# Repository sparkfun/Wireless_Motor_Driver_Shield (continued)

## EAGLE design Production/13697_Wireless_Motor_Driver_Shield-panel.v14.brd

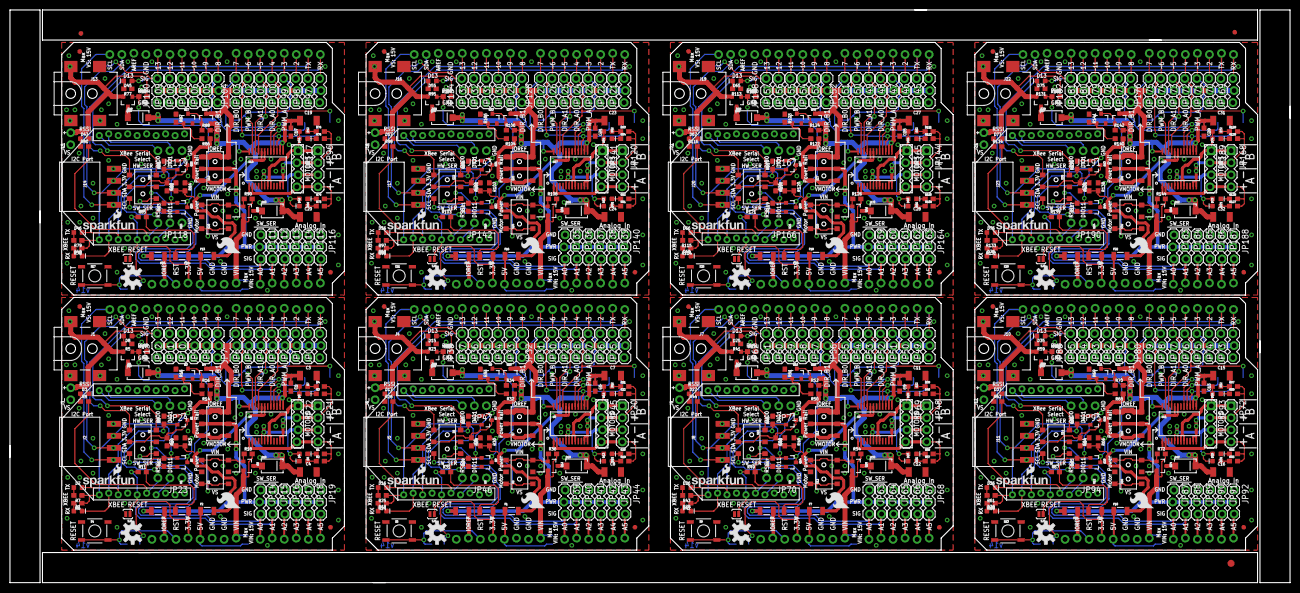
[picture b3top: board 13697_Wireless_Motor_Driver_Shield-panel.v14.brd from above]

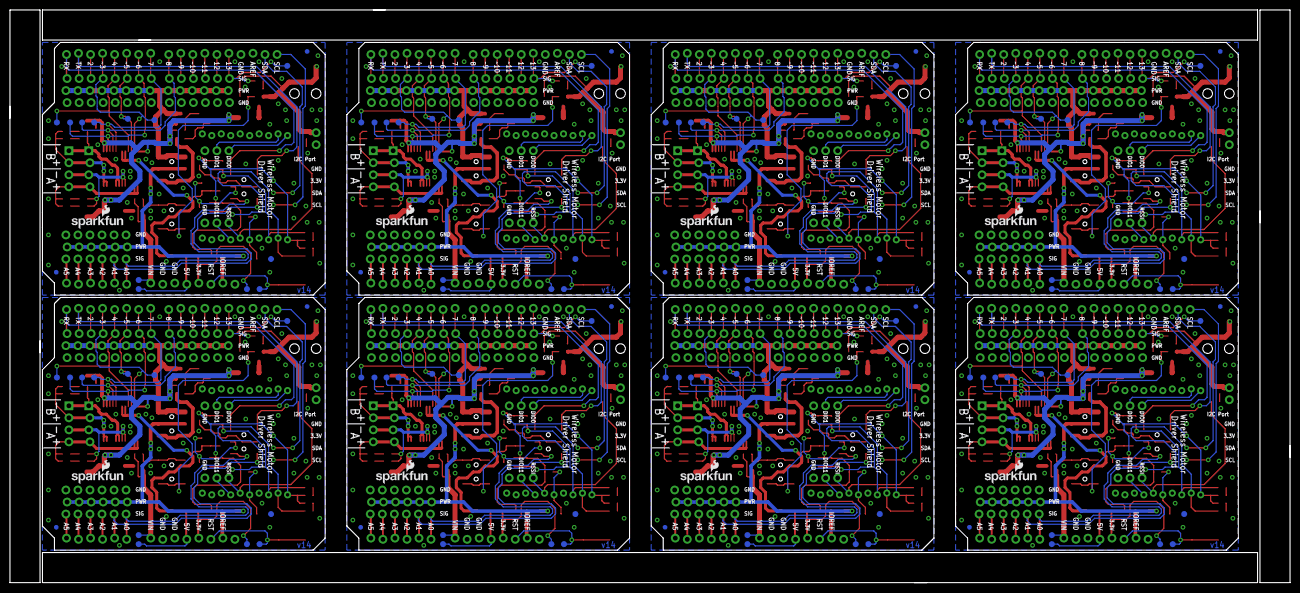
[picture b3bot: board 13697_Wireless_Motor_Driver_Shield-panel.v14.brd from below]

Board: 2 copper layers, 270.3 x 120.9 mm, 771 parts (120 on the bottom side), 496 nets.

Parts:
C1, C2, C5, C6, C9, C10, C13, C14, C17, C18, C21, C22, C25, C26, C29, C30: 0.1uF; 0603
C3, C4, C7, C8, C11, C12, C15, C16, C19, C20, C23, C24, C27, C28, C31, C32: 10uF; 1210
D1, D5, D7, D11, D12, D18, D21, D22, D28, D31, D32, D38, D41, D42, D48, D51, D52, D58, D61, D62, D68, D71, D72, D78: Yellow; LED-0603
D2, D8, D15, D16, D25, D26, D35, D36, D45, D46, D55, D56, D65, D66, D75, D76: GREEN; LED-0603
D3, D17, D27, D37, D47, D57, D67, D77: RED; LED-0603
D4, D6, D13, D14, D23, D24, D33, D34, D43, D44, D53, D54, D63, D64, D73, D74: BLUE; LED-0603
D9, D10, D19, D20, D29, D30, D39, D40, D49, D50, D59, D60, D69, D70, D79, D80: B340A; SMA-DIODE
E$1: FIDUCIAL-1.5X3
E$5, E$6: FIDUCIAL-1X2
F1, F2, F3, F4, F5, F6, F7, F8, F9, F10, F11, F12, F13, F14, F15, F16, F17, F18, F19, F20, F21, F22, F23, F24: PTC-1206
FID1, FID2, FID3, FID4, FID5, FID6, FID7, FID8, FID9, FID10, FID11, FID12, FID13, FID14, FID15, FID16, FID17, FID18, FID19, FID20, FID21, FID22, FID23, FID24, FID25, FID26, FID27, FID28, FID29, FID30, FID31, FID32: FIDUCIAL1X2; FIDUCIAL-1X2
J1, J4, J7, J10, J13, J16, J19, J22: 5.5x2.1mm Barrel; POWER_JACK_SMD
J2, J5, J8, J11, J14, J17, J20, J23: 1X04_SMD_RA_FEMALE
J3, J6, J9, J12, J15, J18, J21, J24: 1X02_NO_SILK
JP0, JP25, JP49, JP73, JP97, JP121, JP145, JP169: D0; 1X03_LOCK
JP1, JP26, JP50, JP74, JP98, JP122, JP146, JP170: D1; 1X03_LOCK
JP2, JP27, JP51, JP75, JP99, JP123, JP147, JP171: D2; 1X03_LOCK
JP3, JP28, JP52, JP76, JP100, JP124, JP148, JP172: D3; 1X03_LOCK
JP4, JP29, JP53, JP77, JP101, JP125, JP149, JP173: D4; 1X03_LOCK
JP5, JP30, JP54, JP78, JP102, JP126, JP150, JP174: D5; 1X03_LOCK
JP6, JP31, JP55, JP79, JP103, JP127, JP151, JP175: D6; 1X03_LOCK
JP7, JP32, JP56, JP80, JP104, JP128, JP152, JP176: D7; 1X03_LOCK
JP8, JP33, JP57, JP81, JP105, JP129, JP153, JP177: D8; 1X03_LOCK
JP9, JP34, JP58, JP82, JP106, JP130, JP154, JP178: D9; 1X03_LOCK
JP10, JP35, JP59, JP83, JP107, JP131, JP155, JP179: D10; 1X03_LOCK
JP11, JP36, JP60, JP84, JP108, JP132, JP156, JP180: D11; 1X03_LOCK
JP12, JP37, JP61, JP85, JP109, JP133, JP157, JP181: D12; 1X03_LOCK
JP13, JP38, JP62, JP86, JP110, JP134, JP158, JP182: D13; 1X03_LOCK
JP14, JP39, JP63, JP87, JP111, JP135, JP159, JP183: A0; 1X03_LOCK
JP15, JP40, JP64, JP88, JP112, JP136, JP160, JP184: A1; 1X03_LOCK
JP16, JP41, JP65, JP89, JP113, JP137, JP161, JP185: A2; 1X03_LOCK
JP17, JP42, JP66, JP90, JP114, JP138, JP162, JP186: A3; 1X03_LOCK
JP18, JP43, JP67, JP91, JP115, JP139, JP163, JP187: A4; 1X03_LOCK
JP19, JP44, JP68, JP92, JP116, JP140, JP164, JP188: A5; 1X03_LOCK
JP20, JP21, JP48, JP72, JP96, JP120, JP144, JP168: 1X04@1
JP22, JP45, JP69, JP93, JP117, JP141, JP165, JP189: 1X04_LOCK@1
JP23, JP24, JP46, JP47, JP70, JP71, JP94, JP95, JP118, JP119, JP142, JP143, JP166, JP167, JP190, JP191: 1X03_NO_SILK
LOGO1, LOGO5, LOGO9, LOGO13, LOGO17, LOGO21, LOGO25, LOGO29: OSHW-LOGOM; OSHW-LOGO-M
LOGO2, LOGO4, LOGO6, LOGO8, LOGO10, LOGO12, LOGO14, LOGO16, LOGO18, LOGO20, LOGO22, LOGO24, LOGO26, LOGO28, LOGO30, LOGO32: SFE_LOGO_NAME_FLAME.1_INCH; SFE_LOGO_NAME_FLAME_.1
LOGO3, LOGO7, LOGO11, LOGO15, LOGO19, LOGO23, LOGO27, LOGO31: SFE_LOGO_FLAME.2_INCH; SFE_LOGO_FLAME_.2
Q1, Q2, Q7, Q8, Q13, Q14, Q19, Q20, Q25, Q26, Q31, Q32, Q37, Q38, Q43, Q44: MOSFET-NCHANNELBSS138; SOT23-3
Q3, Q9, Q15, Q21, Q27, Q33, Q39, Q45: MMBT2222A; SOT23-3
Q4, Q5, Q6, Q10, Q11, Q12, Q16, Q17, Q18, Q22, Q23, Q24, Q28, Q29, Q30, Q34, Q35, Q36, Q40, Q41, Q42, Q46, Q47, Q48: DMG2307L; SOT23-3
R1, R2, R3, R4, R6, R7, R8, R9, R10, R11, R12, R13, R14, R19, R20, R21, R22, R24, R25, R26, R27, R28, R29, R30, R31, R32, R37, R38, R39, R40, R42, R43, R44, R45, R46, R47, R48, R49, R50, R55, R56, R57, R58, R60, R61, R62, R63, R64, R65, R66, R67, R68, R73, R74, R75, R76, R78, R79, R80, R81, R82, R83, R84, R85, R86, R91, R92, R93, R94, R96, R97, R98, R99, R100, R101, R102, R103, R104, R109, R110, R111, R112, R114, R115, R116, R117, R118, R119, R120, R121, R122, R127, R128, R129, R130, R132, R133, R134, R135, R136, R137, R138, R139, R140: 1k; 0603
R5, R23, R41, R59, R77, R95, R113, R131: 330; 0603
R15, R16, R17, R18, R33, R34, R35, R36, R51, R52, R53, R54, R69, R70, R71, R72, R87, R88, R89, R90, R105, R106, R107, R108, R123, R124, R125, R126, R141, R142, R143, R144: 10k; 0603
S1, S3, S7, S8, S11, S12, S15, S16, S19, S20, S23, S24, S27, S28, S31, S32: AYZ0202
S2, S6, S10, S14, S18, S22, S26, S30: DPDT; AYZ0202
S4, S5, S9, S13, S17, S21, S25, S29: RESET; TACTILE-SWITCH-SMD
SJ1, SJ2, SJ3, SJ4, SJ5, SJ6, SJ7, SJ8: SJ_2S-NO
TP1, TP2, TP3, TP4, TP5, TP6, TP7, TP8, TP9, TP10, TP11, TP12, TP13, TP14, TP15, TP16, TP17, TP18, TP19, TP20, TP21, TP22, TP23, TP24, TP25, TP26, TP27, TP28, TP29, TP30, TP31, TP32, TP33, TP34, TP35, TP36, TP37, TP38, TP39, TP40, TP41, TP42, TP43, TP44, TP45, TP46, TP47, TP48, TP49, TP50, TP51, TP52, TP53, TP54, TP55, TP56, TP57, TP58, TP59, TP60, TP61, TP62, TP63, TP64, TP65, TP66, TP67, TP68, TP69, TP70, TP71, TP72, TP73, TP74, TP75, TP76, TP77, TP78, TP79, TP80, TP81, TP82, TP83, TP84, TP85, TP86, TP87, TP88, TP89, TP90, TP91, TP92, TP93, TP94, TP95, TP96: PAD.03X.05
U1, U6, U9, U12, U15, U18, U21, U24: XBEE-1XBEE-1_LOCK; XBEE-1_LOCK
U2, U4, U7, U10, U13, U16, U19, U22: ARDUINO; UNO_R3_SHIELD_NOLABELS_LOCK
U3, U5, U8, U11, U14, U17, U20, U23: TB6612FNG; SSOP24

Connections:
3.3V: F3.1, TP11.P$1, U2.3.3V
3.3V1: F5.1, TP23.P$1, U4.3.3V
3.3V2: F8.1, TP35.P$1, U7.3.3V
3.3V3: F11.1, TP47.P$1, U10.3.3V
3.3V4: F14.1, TP59.P$1, U13.3.3V
3.3V5: F17.1, TP71.P$1, U16.3.3V
3.3V6: F20.1, TP83.P$1, U19.3.3V
3.3V7: F23.1, TP95.P$1, U22.3.3V
5V: F2.1, TP8.P$1, U2.5V
5V1: F1.1, TP20.P$1, U4.5V
5V2: F7.1, TP32.P$1, U7.5V
5V3: F10.1, TP44.P$1, U10.5V
5V4: F13.1, TP56.P$1, U13.5V
5V5: F16.1, TP68.P$1, U16.5V
5V6: F19.1, TP80.P$1, U19.5V
5V7: F22.1, TP92.P$1, U22.5V
A0/SW_RXI: JP14.3, S2.3, U2.A0
A0/SW_RXI1: JP39.3, S6.3, U4.A0
A0/SW_RXI2: JP63.3, S10.3, U7.A0
A0/SW_RXI3: JP87.3, S14.3, U10.A0
A0/SW_RXI4: JP111.3, S18.3, U13.A0
A0/SW_RXI5: JP135.3, S22.3, U16.A0
A0/SW_RXI6: JP159.3, S26.3, U19.A0
A0/SW_RXI7: JP183.3, S30.3, U22.A0
A1: JP44.3, U4.A5
A1/SW_TXO: JP15.3, S2.6, U2.A1
A1/SW_TXO1: JP40.3, S6.6, U4.A1
A1/SW_TXO2: JP64.3, S10.6, U7.A1
A1/SW_TXO3: JP88.3, S14.6, U10.A1
A1/SW_TXO4: JP112.3, S18.6, U13.A1
A1/SW_TXO5: JP136.3, S22.6, U16.A1
A1/SW_TXO6: JP160.3, S26.6, U19.A1
A1/SW_TXO7: JP184.3, S30.6, U22.A1
A2: JP16.3, U2.A2
A3: JP17.3, U2.A3
A4: JP18.3, U2.A4
A5: JP19.3, U2.A5
A6: JP43.3, U4.A4
A7: JP41.3, U4.A2
A8: JP42.3, U4.A3
A9: JP68.3, U7.A5
A10: JP67.3, U7.A4
A11: JP65.3, U7.A2
A12: JP66.3, U7.A3
A13: JP92.3, U10.A5
A14: JP91.3, U10.A4
A15: JP89.3, U10.A2
A16: JP90.3, U10.A3
A17: JP116.3, U13.A5
A18: JP115.3, U13.A4
A19: JP113.3, U13.A2
A20: JP114.3, U13.A3
A21: JP140.3, U16.A5
A22: JP139.3, U16.A4
A23: JP137.3, U16.A2
A24: JP138.3, U16.A3
A25: JP164.3, U19.A5
A26: JP163.3, U19.A4
A27: JP161.3, U19.A2
A28: JP162.3, U19.A3
A29: JP188.3, U22.A5
A30: JP187.3, U22.A4
A31: JP185.3, U22.A2
A32: JP186.3, U22.A3
AIN1: JP4.3, TP1.P$1, U2.D4, U3.21
AIN2: JP5.3, TP2.P$1, U2.D5, U3.22
AIN3: JP30.3, TP14.P$1, U4.D5, U5.22
AIN4: JP29.3, TP13.P$1, U4.D4, U5.21
AIN5: JP54.3, TP26.P$1, U7.D5, U8.22
AIN6: JP53.3, TP25.P$1, U7.D4, U8.21
AIN7: JP78.3, TP38.P$1, U10.D5, U11.22
AIN8: JP77.3, TP37.P$1, U10.D4, U11.21
AIN9: JP102.3, TP50.P$1, U13.D5, U14.22
AIN10: JP101.3, TP49.P$1, U13.D4, U14.21
AIN11: JP126.3, TP62.P$1, U16.D5, U17.22
AIN12: JP125.3, TP61.P$1, U16.D4, U17.21
AIN13: JP150.3, TP74.P$1, U19.D5, U20.22
AIN14: JP149.3, TP73.P$1, U19.D4, U20.21
AIN15: JP174.3, TP86.P$1, U22.D5, U23.22
AIN16: JP173.3, TP85.P$1, U22.D4, U23.21
AOUT1: JP21.4, JP22.4, R1.2, R2.2, U3.1, U3.2
AOUT2: D4.A, D5.C, JP21.3, JP22.3, U3.5, U3.6
AOUT3: JP20.4, JP45.4, R19.2, R20.2, U5.1, U5.2
AOUT4: D11.C, D13.A, JP20.3, JP45.3, U5.5, U5.6
AOUT5: JP48.4, JP69.4, R37.2, R38.2, U8.1, U8.2
AOUT6: D21.C, D23.A, JP48.3, JP69.3, U8.5, U8.6
AOUT7: JP72.4, JP93.4, R55.2, R56.2, U11.1, U11.2
AOUT8: D31.C, D33.A, JP72.3, JP93.3, U11.5, U11.6
AOUT9: JP96.4, JP117.4, R73.2, R74.2, U14.1, U14.2
AOUT10: D41.C, D43.A, JP96.3, JP117.3, U14.5, U14.6
AOUT11: JP120.4, JP141.4, R91.2, R92.2, U17.1, U17.2
AOUT12: D51.C, D53.A, JP120.3, JP141.3, U17.5, U17.6
AOUT13: JP144.4, JP165.4, R109.2, R110.2, U20.1, U20.2
AOUT14: D61.C, D63.A, JP144.3, JP165.3, U20.5, U20.6
AOUT15: JP168.4, JP189.4, R127.2, R128.2, U23.1, U23.2
AOUT16: D71.C, D73.A, JP168.3, JP189.3, U23.5, U23.6
BIN1: JP7.3, TP4.P$1, U2.D7, U3.17
BIN2: JP8.3, TP5.P$1, U2.D8, U3.16
BIN3: JP32.3, TP16.P$1, U4.D7, U5.17
BIN4: JP33.3, TP17.P$1, U4.D8, U5.16
BIN5: JP56.3, TP28.P$1, U7.D7, U8.17
BIN6: JP57.3, TP29.P$1, U7.D8, U8.16
BIN7: JP80.3, TP40.P$1, U10.D7, U11.17
BIN8: JP81.3, TP41.P$1, U10.D8, U11.16
BIN9: JP104.3, TP52.P$1, U13.D7, U14.17
BIN10: JP105.3, TP53.P$1, U13.D8, U14.16
BIN11: JP128.3, TP64.P$1, U16.D7, U17.17
BIN12: JP129.3, TP65.P$1, U16.D8, U17.16
BIN13: JP152.3, TP76.P$1, U19.D7, U20.17
BIN14: JP153.3, TP77.P$1, U19.D8, U20.16
BIN15: JP176.3, TP88.P$1, U22.D7, U23.17
BIN16: JP177.3, TP89.P$1, U22.D8, U23.16
BOUT1: JP21.2, JP22.2, R3.2, R4.2, U3.11, U3.12
BOUT2: D6.A, D7.C, JP21.1, JP22.1, U3.7, U3.8
BOUT3: D12.C, D14.A, JP20.1, JP45.1, U5.7, U5.8
BOUT4: JP20.2, JP45.2, R21.2, R22.2, U5.11, U5.12
BOUT5: D22.C, D24.A, JP48.1, JP69.1, U8.7, U8.8
BOUT6: JP48.2, JP69.2, R39.2, R40.2, U8.11, U8.12
BOUT7: D32.C, D34.A, JP72.1, JP93.1, U11.7, U11.8
BOUT8: JP72.2, JP93.2, R57.2, R58.2, U11.11, U11.12
BOUT9: D42.C, D44.A, JP96.1, JP117.1, U14.7, U14.8
BOUT10: JP96.2, JP117.2, R75.2, R76.2, U14.11, U14.12
BOUT11: D52.C, D54.A, JP120.1, JP141.1, U17.7, U17.8
BOUT12: JP120.2, JP141.2, R93.2, R94.2, U17.11, U17.12
BOUT13: D62.C, D64.A, JP144.1, JP165.1, U20.7, U20.8
BOUT14: JP144.2, JP165.2, R111.2, R112.2, U20.11, U20.12
BOUT15: D72.C, D74.A, JP168.1, JP189.1, U23.7, U23.8
BOUT16: JP168.2, JP189.2, R129.2, R130.2, U23.11, U23.12
D0/RXI: JP0.3, S2.1, U2.RX
D0/RXI1: JP25.3, S6.1, U4.RX
D0/RXI2: JP49.3, S10.1, U7.RX
D0/RXI3: JP73.3, S14.1, U10.RX
D0/RXI4: JP97.3, S18.1, U13.RX
D0/RXI5: JP121.3, S22.1, U16.RX
D0/RXI6: JP145.3, S26.1, U19.RX
D0/RXI7: JP169.3, S30.1, U22.RX
D1: JP37.3, U4.D12
D1/TXO: JP1.3, S2.4, U2.TX
D1/TXO1: JP26.3, S6.4, U4.TX
D1/TXO2: JP50.3, S10.4, U7.TX
D1/TXO3: JP74.3, S14.4, U10.TX
D1/TXO4: JP98.3, S18.4, U13.TX
D1/TXO5: JP122.3, S22.4, U16.TX
D1/TXO6: JP146.3, S26.4, U19.TX
D1/TXO7: JP170.3, S30.4, U22.TX
D2: JP2.3, U2.D2
D3: D15.A, JP38.3, TP19.P$1, U4.D13
D4: JP35.3, U4.D10
D5: JP27.3, U4.D2
D6: JP36.3, U4.D11
D7: JP34.3, U4.D9
D8: JP61.3, U7.D12
D9: JP9.3, U2.D9
D10: JP10.3, U2.D10
D11: JP11.3, U2.D11
D12: JP12.3, U2.D12
D13: D8.A, JP13.3, TP7.P$1, U2.D13
D14: D25.A, JP62.3, TP31.P$1, U7.D13
D15: JP59.3, U7.D10
D16: JP51.3, U7.D2
D17: JP60.3, U7.D11
D18: JP58.3, U7.D9
D19: JP85.3, U10.D12
D20: D35.A, JP86.3, TP43.P$1, U10.D13
D21: JP83.3, U10.D10
D22: JP75.3, U10.D2
D23: JP84.3, U10.D11
D24: JP82.3, U10.D9
D25: JP109.3, U13.D12
D26: D45.A, JP110.3, TP55.P$1, U13.D13
D27: JP107.3, U13.D10
D28: JP99.3, U13.D2
D29: JP108.3, U13.D11
D30: JP106.3, U13.D9
D31: JP133.3, U16.D12
D32: D55.A, JP134.3, TP67.P$1, U16.D13
D33: JP131.3, U16.D10
D34: JP123.3, U16.D2
D35: JP132.3, U16.D11
D36: JP130.3, U16.D9
D37: JP157.3, U19.D12
D38: D65.A, JP158.3, TP79.P$1, U19.D13
D39: JP155.3, U19.D10
D40: JP147.3, U19.D2
D41: JP156.3, U19.D11
D42: JP154.3, U19.D9
D43: JP181.3, U22.D12
D44: D75.A, JP182.3, TP91.P$1, U22.D13
D45: JP179.3, U22.D10
D46: JP171.3, U22.D2
D47: JP180.3, U22.D11
D48: JP178.3, U22.D9
DIN: D2.C, Q1.2, R9.1, U1.3
DIN1: D16.C, Q7.2, R27.1, U6.3
DIN2: D26.C, Q13.2, R45.1, U9.3
DIN3: D36.C, Q19.2, R63.1, U12.3
DIN4: D46.C, Q25.2, R81.1, U15.3
DIN5: D56.C, Q31.2, R99.1, U18.3
DIN6: D66.C, Q37.2, R117.1, U21.3
DIN7: D76.C, Q43.2, R135.1, U24.3
DIO0: JP24.3, U1.20
DIO1: JP24.2, U1.19
DIO2: JP46.2, U6.7
DIO3: JP47.3, U6.20
DIO4: JP47.2, U6.19
DIO5: JP70.2, U9.7
DIO6: JP71.3, U9.20
DIO7: JP71.2, U9.19
DIO8: JP94.2, U12.7
DIO9: JP95.3, U12.20
DIO10: JP95.2, U12.19
DIO11: JP23.2, U1.7
DIO12: JP118.2, U15.7
DIO13: JP119.3, U15.20
DIO14: JP119.2, U15.19
DIO15: JP142.2, U18.7
DIO16: JP143.3, U18.20
DIO17: JP143.2, U18.19
DIO18: JP166.2, U21.7
DIO19: JP167.3, U21.20
DIO20: JP167.2, U21.19
DIO21: JP190.2, U24.7
DIO22: JP191.3, U24.20
DIO23: JP191.2, U24.19
DOUT: D1.C, Q2.2, R12.1, U1.2
DOUT1: D18.C, Q8.2, R29.1, U6.2
DOUT2: D28.C, Q14.2, R47.1, U9.2
DOUT3: D38.C, Q20.2, R65.1, U12.2
DOUT4: D48.C, Q26.2, R83.1, U15.2
DOUT5: D58.C, Q32.2, R101.1, U18.2
DOUT6: D68.C, Q38.2, R119.1, U21.2
DOUT7: D78.C, Q44.2, R137.1, U24.2
FUSED_3.3V: F3.2, J2.2, Q1.1, Q2.1, R6.1, R7.1, R9.2, R11.2, R12.2, U1.1
FUSED_3.3V1: F5.2, J5.2, Q7.1, Q8.1, R24.1, R25.1, R27.2, R29.2, R31.2, U6.1
FUSED_3.3V2: F8.2, J8.2, Q13.1, Q14.1, R42.1, R43.1, R45.2, R47.2, R49.2, U9.1
FUSED_3.3V3: F11.2, J11.2, Q19.1, Q20.1, R60.1, R61.1, R63.2, R65.2, R67.2, U12.1
FUSED_3.3V4: F14.2, J14.2, Q25.1, Q26.1, R78.1, R79.1, R81.2, R83.2, R85.2, U15.1
FUSED_3.3V5: F17.2, J17.2, Q31.1, Q32.1, R96.1, R97.1, R99.2, R101.2, R103.2, U18.1
FUSED_3.3V6: F20.2, J20.2, Q37.1, Q38.1, R114.1, R115.1, R117.2, R119.2, R121.2, U21.1
FUSED_3.3V7: F23.2, J23.2, Q43.1, Q44.1, R132.1, R133.1, R135.2, R137.2, R139.2, U24.1
FUSED_5V: C2.1, F2.2, R10.2, R13.2, U3.19, U3.20
FUSED_5V1: C6.1, F1.2, R28.2, R30.2, U5.19, U5.20
FUSED_5V2: C10.1, F7.2, R46.2, R48.2, U8.19, U8.20
FUSED_5V3: C14.1, F10.2, R64.2, R66.2, U11.19, U11.20
FUSED_5V4: C18.1, F13.2, R82.2, R84.2, U14.19, U14.20
FUSED_5V5: C22.1, F16.2, R100.2, R102.2, U17.19, U17.20
FUSED_5V6: C26.1, F19.2, R118.2, R120.2, U20.19, U20.20
FUSED_5V7: C30.1, F22.2, R136.2, R138.2, U23.19, U23.20
FUSED_IOREF: F4.2, JP14.2, JP15.2, JP16.2, JP17.2, JP18.2, JP19.2, S1.2, S1.5
FUSED_IOREF1: F6.2, JP39.2, JP40.2, JP41.2, JP42.2, JP43.2, JP44.2, S7.2, S7.5
FUSED_IOREF2: F9.2, JP63.2, JP64.2, JP65.2, JP66.2, JP67.2, JP68.2, S11.2, S11.5
FUSED_IOREF3: F12.2, JP87.2, JP88.2, JP89.2, JP90.2, JP91.2, JP92.2, S15.2, S15.5
FUSED_IOREF4: F15.2, JP111.2, JP112.2, JP113.2, JP114.2, JP115.2, JP116.2, S19.2, S19.5
FUSED_IOREF5: F18.2, JP135.2, JP136.2, JP137.2, JP138.2, JP139.2, JP140.2, S23.2, S23.5
FUSED_IOREF6: F21.2, JP159.2, JP160.2, JP161.2, JP162.2, JP163.2, JP164.2, S27.2, S27.5
FUSED_IOREF7: F24.2, JP183.2, JP184.2, JP185.2, JP186.2, JP187.2, JP188.2, S31.2, S31.5
GND: C1.2, C2.2, C3.2, C4.2, D3.C, J1.GND, J2.1, J3.1, JP0.1, JP1.1, JP2.1, JP3.1, JP4.1, JP5.1, JP6.1, JP7.1, JP8.1, JP9.1, JP10.1, JP11.1, JP12.1, JP13.1, JP14.1, JP15.1, JP16.1, JP17.1, JP18.1, JP19.1, JP23.1, JP24.1, Q3.2, R5.1, R15.1, S3.2, S3.5, S4.1, S4.2, SJ5.2, TP9.P$1, U1.10, U2.GND@0, U2.GND@1, U2.GND@2, U3.3, U3.4, U3.9, U3.10, U3.18
GND1: C5.2, C6.2, C7.2, C8.2, D17.C, J4.GND, J5.1, J6.1, JP25.1, JP26.1, JP27.1, JP28.1, JP29.1, JP30.1, JP31.1, JP32.1, JP33.1, JP34.1, JP35.1, JP36.1, JP37.1, JP38.1, JP39.1, JP40.1, JP41.1, JP42.1, JP43.1, JP44.1, JP46.1, JP47.1, Q9.2, R23.1, R33.1, S5.1, S5.2, S8.2, S8.5, SJ1.2, TP21.P$1, U4.GND@0, U4.GND@1, U4.GND@2, U5.3, U5.4, U5.9, U5.10, U5.18, U6.10
GND2: C9.2, C10.2, C11.2, C12.2, D27.C, J7.GND, J8.1, J9.1, JP49.1, JP50.1, JP51.1, JP52.1, JP53.1, JP54.1, JP55.1, JP56.1, JP57.1, JP58.1, JP59.1, JP60.1, JP61.1, JP62.1, JP63.1, JP64.1, JP65.1, JP66.1, JP67.1, JP68.1, JP70.1, JP71.1, Q15.2, R41.1, R51.1, S9.1, S9.2, S12.2, S12.5, SJ2.2, TP33.P$1, U7.GND@0, U7.GND@1, U7.GND@2, U8.3, U8.4, U8.9, U8.10, U8.18, U9.10
GND3: C13.2, C14.2, C15.2, C16.2, D37.C, J10.GND, J11.1, J12.1, JP73.1, JP74.1, JP75.1, JP76.1, JP77.1, JP78.1, JP79.1, JP80.1, JP81.1, JP82.1, JP83.1, JP84.1, JP85.1, JP86.1, JP87.1, JP88.1, JP89.1, JP90.1, JP91.1, JP92.1, JP94.1, JP95.1, Q21.2, R59.1, R69.1, S13.1, S13.2, S16.2, S16.5, SJ3.2, TP45.P$1, U10.GND@0, U10.GND@1, U10.GND@2, U11.3, U11.4, U11.9, U11.10, U11.18, U12.10
GND4: C17.2, C18.2, C19.2, C20.2, D47.C, J13.GND, J14.1, J15.1, JP97.1, JP98.1, JP99.1, JP100.1, JP101.1, JP102.1, JP103.1, JP104.1, JP105.1, JP106.1, JP107.1, JP108.1, JP109.1, JP110.1, JP111.1, JP112.1, JP113.1, JP114.1, JP115.1, JP116.1, JP118.1, JP119.1, Q27.2, R77.1, R87.1, S17.1, S17.2, S20.2, S20.5, SJ4.2, TP57.P$1, U13.GND@0, U13.GND@1, U13.GND@2, U14.3, U14.4, U14.9, U14.10, U14.18, U15.10
GND5: C21.2, C22.2, C23.2, C24.2, D57.C, J16.GND, J17.1, J18.1, JP121.1, JP122.1, JP123.1, JP124.1, JP125.1, JP126.1, JP127.1, JP128.1, JP129.1, JP130.1, JP131.1, JP132.1, JP133.1, JP134.1, JP135.1, JP136.1, JP137.1, JP138.1, JP139.1, JP140.1, JP142.1, JP143.1, Q33.2, R95.1, R105.1, S21.1, S21.2, S24.2, S24.5, SJ6.2, TP69.P$1, U16.GND@0, U16.GND@1, U16.GND@2, U17.3, U17.4, U17.9, U17.10, U17.18, U18.10
GND6: C25.2, C26.2, C27.2, C28.2, D67.C, J19.GND, J20.1, J21.1, JP145.1, JP146.1, JP147.1, JP148.1, JP149.1, JP150.1, JP151.1, JP152.1, JP153.1, JP154.1, JP155.1, JP156.1, JP157.1, JP158.1, JP159.1, JP160.1, JP161.1, JP162.1, JP163.1, JP164.1, JP166.1, JP167.1, Q39.2, R113.1, R123.1, S25.1, S25.2, S28.2, S28.5, SJ7.2, TP81.P$1, U19.GND@0, U19.GND@1, U19.GND@2, U20.3, U20.4, U20.9, U20.10, U20.18, U21.10
GND7: C29.2, C30.2, C31.2, C32.2, D77.C, J22.GND, J23.1, J24.1, JP169.1, JP170.1, JP171.1, JP172.1, JP173.1, JP174.1, JP175.1, JP176.1, JP177.1, JP178.1, JP179.1, JP180.1, JP181.1, JP182.1, JP183.1, JP184.1, JP185.1, JP186.1, JP187.1, JP188.1, JP190.1, JP191.1, Q45.2, R131.1, R141.1, S29.1, S29.2, S32.2, S32.5, SJ8.2, TP93.P$1, U22.GND@0, U22.GND@1, U22.GND@2, U23.3, U23.4, U23.9, U23.10, U23.18, U24.10
IOREF: F4.1, U2.IOREF
IOREF1: F6.1, U4.IOREF
IOREF2: F9.1, U7.IOREF
IOREF3: F12.1, U10.IOREF
IOREF4: F15.1, U13.IOREF
IOREF5: F18.1, U16.IOREF
IOREF6: F21.1, U19.IOREF
IOREF7: F24.1, U22.IOREF
unnamed: D8.C, R5.2
unnamed: Q3.1, R14.2, R15.2
unnamed: D5.A, R2.1
unnamed: Q6.1, R18.1, S3.3, S3.6
unnamed: D4.C, R1.1
unnamed: D7.A, R4.1
unnamed: D6.C, R3.1
unnamed: J1.VIN0, J3.2, Q5.2, R17.2
unnamed: Q3.3, Q4.1, R16.1
unnamed: Q5.1, R17.1, S3.1, S3.4
unnamed: R14.1, S1.1, S1.4
unnamed: D9.A, Q5.3
unnamed: D10.A, Q6.3
unnamed: D11.A, R19.1
unnamed: D13.C, R20.1
unnamed: D12.A, R21.1
unnamed: D14.C, R22.1
unnamed: D15.C, R23.2
unnamed: D1.A, R6.2
unnamed: D18.A, R24.2
unnamed: D16.A, R25.2
unnamed: D17.A, R26.1
unnamed: Q9.1, R32.2, R33.2
unnamed: Q9.3, Q10.1, R34.1
unnamed: R32.1, S7.1, S7.4
unnamed: J4.VIN0, J6.2, Q11.2, R35.2
unnamed: Q11.1, R35.1, S8.1, S8.4
unnamed: Q12.1, R36.1, S8.3, S8.6
unnamed: D19.A, Q11.3
unnamed: D20.A, Q12.3
unnamed: D21.A, R37.1
unnamed: D23.C, R38.1
unnamed: D22.A, R39.1
unnamed: D24.C, R40.1
unnamed: D25.C, R41.2
unnamed: D28.A, R42.2
unnamed: D26.A, R43.2
unnamed: D27.A, R44.1
unnamed: D2.A, R7.2
unnamed: D3.A, R8.1
unnamed: Q15.1, R50.2, R51.2
unnamed: Q15.3, Q16.1, R52.1
unnamed: R50.1, S11.1, S11.4
unnamed: J7.VIN0, J9.2, Q17.2, R53.2
unnamed: Q17.1, R53.1, S12.1, S12.4
unnamed: Q18.1, R54.1, S12.3, S12.6
unnamed: D29.A, Q17.3
unnamed: D30.A, Q18.3
unnamed: D31.A, R55.1
unnamed: D33.C, R56.1
unnamed: D32.A, R57.1
unnamed: D34.C, R58.1
unnamed: D35.C, R59.2
unnamed: D38.A, R60.2
unnamed: D36.A, R61.2
unnamed: D37.A, R62.1
unnamed: Q21.1, R68.2, R69.2
unnamed: Q21.3, Q22.1, R70.1
unnamed: R68.1, S15.1, S15.4
unnamed: J10.VIN0, J12.2, Q23.2, R71.2
unnamed: Q23.1, R71.1, S16.1, S16.4
unnamed: Q24.1, R72.1, S16.3, S16.6
unnamed: D39.A, Q23.3
unnamed: D40.A, Q24.3
unnamed: D41.A, R73.1
unnamed: D43.C, R74.1
unnamed: D42.A, R75.1
unnamed: D44.C, R76.1
unnamed: D45.C, R77.2
unnamed: D48.A, R78.2
unnamed: D46.A, R79.2
unnamed: D47.A, R80.1
unnamed: Q27.1, R86.2, R87.2
unnamed: Q27.3, Q28.1, R88.1
unnamed: R86.1, S19.1, S19.4
unnamed: J13.VIN0, J15.2, Q29.2, R89.2
unnamed: Q29.1, R89.1, S20.1, S20.4
unnamed: Q30.1, R90.1, S20.3, S20.6
unnamed: D49.A, Q29.3
unnamed: D50.A, Q30.3
unnamed: D51.A, R91.1
unnamed: D53.C, R92.1
unnamed: D52.A, R93.1
unnamed: D54.C, R94.1
unnamed: D55.C, R95.2
unnamed: D58.A, R96.2
unnamed: D56.A, R97.2
unnamed: D57.A, R98.1
unnamed: Q33.1, R104.2, R105.2
unnamed: Q33.3, Q34.1, R106.1
unnamed: R104.1, S23.1, S23.4
unnamed: J16.VIN0, J18.2, Q35.2, R107.2
unnamed: Q35.1, R107.1, S24.1, S24.4
unnamed: Q36.1, R108.1, S24.3, S24.6
unnamed: D59.A, Q35.3
unnamed: D60.A, Q36.3
unnamed: D61.A, R109.1
unnamed: D63.C, R110.1
unnamed: D62.A, R111.1
unnamed: D64.C, R112.1
unnamed: D65.C, R113.2
unnamed: D68.A, R114.2
unnamed: D66.A, R115.2
unnamed: D67.A, R116.1
unnamed: Q39.1, R122.2, R123.2
unnamed: Q39.3, Q40.1, R124.1
unnamed: R122.1, S27.1, S27.4
unnamed: J19.VIN0, J21.2, Q41.2, R125.2
unnamed: Q41.1, R125.1, S28.1, S28.4
unnamed: Q42.1, R126.1, S28.3, S28.6
unnamed: D69.A, Q41.3
unnamed: D70.A, Q42.3
unnamed: D71.A, R127.1
unnamed: D73.C, R128.1
unnamed: D72.A, R129.1
unnamed: D74.C, R130.1
unnamed: D75.C, R131.2
unnamed: D78.A, R132.2
unnamed: D76.A, R133.2
unnamed: D77.A, R134.1
unnamed: Q45.1, R140.2, R141.2
unnamed: Q45.3, Q46.1, R142.1
unnamed: R140.1, S31.1, S31.4
unnamed: J22.VIN0, J24.2, Q47.2, R143.2
unnamed: Q47.1, R143.1, S32.1, S32.4
unnamed: Q48.1, R144.1, S32.3, S32.6
unnamed: D79.A, Q47.3
unnamed: D80.A, Q48.3
PWMA: JP3.3, TP3.P$1, U2.D3, U3.23
PWMA1: JP28.3, TP15.P$1, U4.D3, U5.23
PWMA2: JP52.3, TP27.P$1, U7.D3, U8.23
PWMA3: JP76.3, TP39.P$1, U10.D3, U11.23
PWMA4: JP100.3, TP51.P$1, U13.D3, U14.23
PWMA5: JP124.3, TP63.P$1, U16.D3, U17.23
PWMA6: JP148.3, TP75.P$1, U19.D3, U20.23
PWMA7: JP172.3, TP87.P$1, U22.D3, U23.23
PWMB: JP6.3, TP6.P$1, U2.D6, U3.15
PWMB1: JP31.3, TP18.P$1, U4.D6, U5.15
PWMB2: JP55.3, TP30.P$1, U7.D6, U8.15
PWMB3: JP79.3, TP42.P$1, U10.D6, U11.15
PWMB4: JP103.3, TP54.P$1, U13.D6, U14.15
PWMB5: JP127.3, TP66.P$1, U16.D6, U17.15
PWMB6: JP151.3, TP78.P$1, U19.D6, U20.15
PWMB7: JP175.3, TP90.P$1, U22.D6, U23.15
PWR_RAIL: JP0.2, JP1.2, JP2.2, JP3.2, JP4.2, JP5.2, JP6.2, JP7.2, JP8.2, JP9.2, JP10.2, JP11.2, JP12.2, JP13.2, Q4.3, S1.3, S1.6
PWR_RAIL1: JP25.2, JP26.2, JP27.2, JP28.2, JP29.2, JP30.2, JP31.2, JP32.2, JP33.2, JP34.2, JP35.2, JP36.2, JP37.2, JP38.2, Q10.3, S7.3, S7.6
PWR_RAIL2: JP49.2, JP50.2, JP51.2, JP52.2, JP53.2, JP54.2, JP55.2, JP56.2, JP57.2, JP58.2, JP59.2, JP60.2, JP61.2, JP62.2, Q16.3, S11.3, S11.6
PWR_RAIL3: JP73.2, JP74.2, JP75.2, JP76.2, JP77.2, JP78.2, JP79.2, JP80.2, JP81.2, JP82.2, JP83.2, JP84.2, JP85.2, JP86.2, Q22.3, S15.3, S15.6
PWR_RAIL4: JP97.2, JP98.2, JP99.2, JP100.2, JP101.2, JP102.2, JP103.2, JP104.2, JP105.2, JP106.2, JP107.2, JP108.2, JP109.2, JP110.2, Q28.3, S19.3, S19.6
PWR_RAIL5: JP121.2, JP122.2, JP123.2, JP124.2, JP125.2, JP126.2, JP127.2, JP128.2, JP129.2, JP130.2, JP131.2, JP132.2, JP133.2, JP134.2, Q34.3, S23.3, S23.6
PWR_RAIL6: JP145.2, JP146.2, JP147.2, JP148.2, JP149.2, JP150.2, JP151.2, JP152.2, JP153.2, JP154.2, JP155.2, JP156.2, JP157.2, JP158.2, Q40.3, S27.3, S27.6
PWR_RAIL7: JP169.2, JP170.2, JP171.2, JP172.2, JP173.2, JP174.2, JP175.2, JP176.2, JP177.2, JP178.2, JP179.2, JP180.2, JP181.2, JP182.2, Q46.3, S31.3, S31.6
RESET: S4.3, S4.4, TP12.P$1, U2.RES
RESET1: S5.3, S5.4, TP24.P$1, U4.RES
RESET2: S9.3, S9.4, TP36.P$1, U7.RES
RESET3: S13.3, S13.4, TP48.P$1, U10.RES
RESET4: S17.3, S17.4, TP60.P$1, U13.RES
RESET5: S21.3, S21.4, TP72.P$1, U16.RES
RESET6: S25.3, S25.4, TP84.P$1, U19.RES
RESET7: S29.3, S29.4, TP96.P$1, U22.RES
RSSI: JP23.3, R8.2, U1.6
RSSI1: JP46.3, R26.2, U6.6
RSSI2: JP70.3, R44.2, U9.6
RSSI3: JP94.3, R62.2, U12.6
RSSI4: JP118.3, R80.2, U15.6
RSSI5: JP142.3, R98.2, U18.6
RSSI6: JP166.3, R116.2, U21.6
RSSI7: JP190.3, R134.2, U24.6
SCL: J2.4, U2.SCL
SCL1: J5.4, U4.SCL
SCL2: J8.4, U7.SCL
SCL3: J11.4, U10.SCL
SCL4: J14.4, U13.SCL
SCL5: J17.4, U16.SCL
SCL6: J20.4, U19.SCL
SCL7: J23.4, U22.SCL
SDA: J2.3, U2.SDA
SDA1: J5.3, U4.SDA
SDA2: J8.3, U7.SDA
SDA3: J11.3, U10.SDA
SDA4: J14.3, U13.SDA
SDA5: J17.3, U16.SDA
SDA6: J20.3, U19.SDA
SDA7: J23.3, U22.SDA
VIN: Q6.2, R18.2, TP10.P$1, U2.VIN
VIN1: Q12.2, R36.2, TP22.P$1, U4.VIN
VIN2: Q18.2, R54.2, TP34.P$1, U7.VIN
VIN3: Q24.2, R72.2, TP46.P$1, U10.VIN
VIN4: Q30.2, R90.2, TP58.P$1, U13.VIN
VIN5: Q36.2, R108.2, TP70.P$1, U16.VIN
VIN6: Q42.2, R126.2, TP82.P$1, U19.VIN
VIN7: Q48.2, R144.2, TP94.P$1, U22.VIN
VMOTOR: C1.1, C3.1, C4.1, D9.C, D10.C, Q4.2, R16.2, U3.13, U3.14, U3.24
VMOTOR1: C5.1, C7.1, C8.1, D19.C, D20.C, Q10.2, R34.2, U5.13, U5.14, U5.24
VMOTOR2: C9.1, C11.1, C12.1, D29.C, D30.C, Q16.2, R52.2, U8.13, U8.14, U8.24
VMOTOR3: C13.1, C15.1, C16.1, D39.C, D40.C, Q22.2, R70.2, U11.13, U11.14, U11.24
VMOTOR4: C17.1, C19.1, C20.1, D49.C, D50.C, Q28.2, R88.2, U14.13, U14.14, U14.24
VMOTOR5: C21.1, C23.1, C24.1, D59.C, D60.C, Q34.2, R106.2, U17.13, U17.14, U17.24
VMOTOR6: C25.1, C27.1, C28.1, D69.C, D70.C, Q40.2, R124.2, U20.13, U20.14, U20.24
VMOTOR7: C29.1, C31.1, C32.1, D79.C, D80.C, Q46.2, R142.2, U23.13, U23.14, U23.24
XBEE_RESET: R11.1, SJ5.1, U1.5
XBEE_RESET1: R31.1, SJ1.1, U6.5
XBEE_RESET2: R49.1, SJ2.1, U9.5
XBEE_RESET3: R67.1, SJ3.1, U12.5
XBEE_RESET4: R85.1, SJ4.1, U15.5
XBEE_RESET5: R103.1, SJ6.1, U18.5
XBEE_RESET6: R121.1, SJ7.1, U21.5
XBEE_RESET7: R139.1, SJ8.1, U24.5
XBEE_RXI: Q2.3, R13.1, S2.2
XBEE_RXI1: Q8.3, R30.1, S6.2
XBEE_RXI2: Q14.3, R48.1, S10.2
XBEE_RXI3: Q20.3, R66.1, S14.2
XBEE_RXI4: Q26.3, R84.1, S18.2
XBEE_RXI5: Q32.3, R102.1, S22.2
XBEE_RXI6: Q38.3, R120.1, S26.2
XBEE_RXI7: Q44.3, R138.1, S30.2
XBEE_TXO: Q1.3, R10.1, S2.5
XBEE_TXO1: Q7.3, R28.1, S6.5
XBEE_TXO2: Q13.3, R46.1, S10.5
XBEE_TXO3: Q19.3, R64.1, S14.5
XBEE_TXO4: Q25.3, R82.1, S18.5
XBEE_TXO5: Q31.3, R100.1, S22.5
XBEE_TXO6: Q37.3, R118.1, S26.5
XBEE_TXO7: Q43.3, R136.1, S30.5
